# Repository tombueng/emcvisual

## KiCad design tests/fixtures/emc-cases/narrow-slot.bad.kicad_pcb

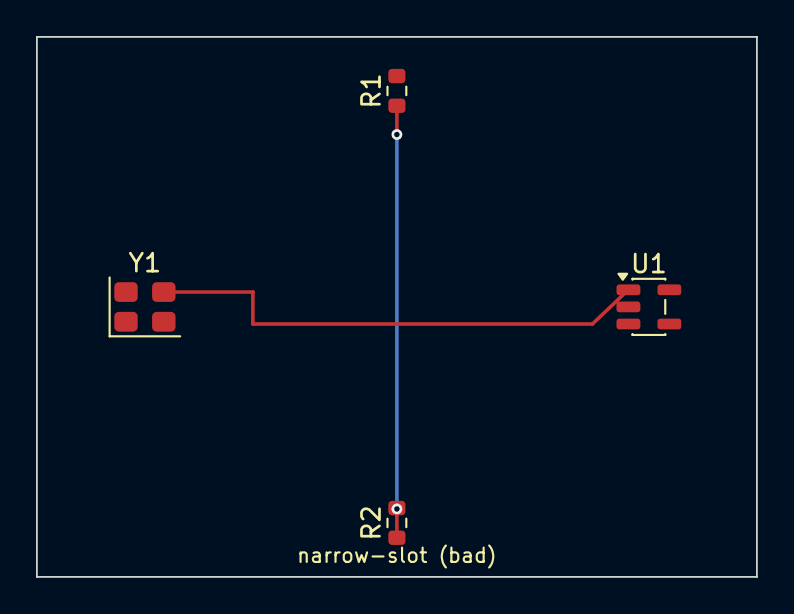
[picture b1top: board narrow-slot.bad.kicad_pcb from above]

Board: 2 copper layers, 40.0 x 30.0 mm, 4 parts (0 on the bottom side), 4 nets.

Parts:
R1, R2: 10k; R_0603_1608Metric
U1: 74LVC1G04; SOT-23-5
Y1: 25MHz; Oscillator_SMD_Abracon_ASE-4Pin_3.2x2.5mm

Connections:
+3V3: U1.5, Y1.1, Y1.4
CLK: U1.1, Y1.3
GND: U1.2, Y1.2
SIG: R1.1, R2.1
